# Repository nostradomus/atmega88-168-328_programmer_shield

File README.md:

# Atmega88/168/328 ISP programmer shield for Arduino UNO boards
  and    (minimal)

## What

This repo provides you with all necessary info (and files) to build an Arduino shield to program [Atmel](http://www.atmel.com)'s **[atmega88/168/328](http://www.microchip.com/design-centers/8-bit/microchip-avr-mcus)** 𝜇-controllers. For that matter, the underlying Arduino board should be loaded with the [ISP-programmer sketch](source/ArduinoISP.ino) (built-in example). Two versions have been included. All images in the description below, refer to the 16MHz version with an external crystal oscillator. An alternative (minimalistic) version is also available in all respective sub-folders (marked as 'minimal'). It concerns a shield to program the same µ-controllers using their 8MHz internal clock.

## Why

After having tested one of your new marvelous ideas with an existing eco-system, a lot of airwires and a piece of breadboard, you will probably start designing a state-of-the-art custom pcb to finalize the building of your project. During such a design phase, I however got tired of wiring up the ISPC connector over-and-over-again. As (like many people) I was having a spare UNO, which could serve as an [in-circuit serial programmer](https://en.wikipedia.org/wiki/In-system_programming), I decided to design a minimalistic shield to fit on top of it.  

## How

The shield has been designed with EAGLE from AutoDesk/CadSoft. This shield [project](eagle-files/) can be opened with the free version [(download here)](http://www.autodesk.com/products/eagle/free-download). Only [through-hole components](BOM.md) have been used in order to make the build also feasible for any junior electronics enthusiast. In the [pdf-folder](pdf-files/) of this repo pdf versions of all important EAGLE views are available, for those not wanting to install EAGLE. Pay attention to print the bottom and top-layer layouts **without re-sizing** (1:1). To have the printed circuit board built by a commercial PCB-shop, the full  [gerber-files](gerber-files/) are also available. When etching the board at home, don't forget to add the vias, or solder pieces of wire from solder to component side.

Currently, unpopulated boards for both the full and minimalistic version are still available from our workshop. If interested, [contact us via   :email:](http://nostradomus.ddns.net/contactform.html).

## Technical details

### What’s on the board

The board has been fit with a narrow 28-pin [ZIF](https://en.wikipedia.org/wiki/Zero_insertion_force) socket, which is wired up to be universal for several types of AVR's. On the boarder of the PCB, pin headers with double functionality have been mounted. Pins on the bottom-side to fit on the Arduino board, and feed-through female headers on the top for easy access of all Arduino connections.
The push button, is connected to the reset lines of the [AVR](https://en.wikipedia.org/wiki/Atmel_AVR) in the ZIF socket (and the ICSP on the shield) with a 10kΩ pull-up resistor. When the shield is cut correctly, the reset button for the underlying Arduino UNO should still be accessible. In order to make the Arduino Uno work as an ISP programmer a 10µF capacitor needs to be connected on its reset-line.
Three LED’s are available to visualize the correct functionality of the programming procedure.
An optional AVR ISP connector has been foreseen in order to use the shield as stand-alone with a commercial programmer.

#### BOM - bill of materials

Part   | Value          | Package      | Description  
------ | -------------- | ------------ | -----------                            
R1     | 10kΩ           | 0207/7       | resistor                                            
R2,3,4 | 470Ω           | 0204/5       | resistor                                            
C1     | 10µF/16V       | E2,5-6E      | polarized capacitor                                 
C2     | 100nF          | C050-025X075 | capacitor                                           
C3,4   | 22pF           | C2.5-2       | capacitor (version with xtal-oscillator)                                          
X1     | 16MHz          | QS           | oscillator crystal (version with xtal-oscillator)
LED1   | 3mm yellow     | 3mm          | LED                              
LED2   | 3mm red        | 3mm          | LED                              
LED3   | 3mm green      | 3mm          | LED
IC1    | 28-pin         | ZIF28-N      | 28-pin narrow ZIF-socket
ICSP1  | 2x3 pin-header | 2x3          | AVR ISP-6 Serial Programming Header (optional)
S1     | momentary      | 6x6x6mm      | momentary tact push button
S2     | toggle         | 9x4mm        | mini toggle switch
CON1   | 6-pin          | SIL06        | long needle female stackable pin header strip
CON2,3 | 8-pin          | SIL08        | long needle female stackable pin header strip
CON4   | 10-pin         | SIL10        | long needle female stackable pin header strip

### How things work

First the the [ISP-programmer sketch](sketches/ArduinoISP.ino) (built-in example) should be loaded to the Arduino UNO board. During that operation, switch S2 should be set to "RUN". Select “Arduino Uno” as target board in the tools-menu. Load the ISP-programmer sketch with the “UPLOAD” button. Once loaded, switch S2 can be set to "PROG" to send a sketch to the atmega 𝜇-controller in the ZIF socket.

To load a sketch to your atmega 𝜇-controller in the ZIF socket, make sure that the correct target board is selected in the tools-menu (you might need to download a specific library -> tools-menu, board manager). This time, use the “UPLOAD USING PROGRAMMER” option from the sketch-menu.

When using the "8MHz internal clock" shield, an [adapted board configuration](source/minimal-boards.zip) should be used (read "fuse-settings"), which can be found in the [source-folder](source/). Other versions can be found on the [Arduino website](https://www.arduino.cc/en/Tutorial/ArduinoToBreadboard) (see paragraph on minimal hardware). To install this package driver, create a "hardware" folder in the Arduino sketches folder on your computer (path to be found in the Arduino preferences),

and copy the unzipped [package archive](source/minimal-boards.zip) in there.

Next restart the Arduino IDE, and the required board will appear in your board's list.

When loading a new sketch to the target µ-controller, the 3 LED’s will tell you how things are going :
 - Green  : **ICSP programmer running** (fading LED means 'idle')
 - Yellow : **uploading sketch** (programming code is being uploaded)
 - Red    : **Error!** (oops, something went wrong during the upload)

### Proof of concept

So far, I have tested the shield with the below list of 𝜇-controllers :
- atmega168
- atmega328

 Programming shield should also function correctly for other pin-compatible µ-controllers, such as :
 - atmega88

## Contributors

If you are having any good suggestions, just drop me a line [:email:](http://nostradomus.ddns.net/contactform.html).
If feasible, I'll be happy to implement any proposed improvements.
And if you are having lots of time, I'll be happy to share the work with you ;-).

When you create your own version, don't forget to send us some nice pictures of your construction. We'll be happy to publish them in the :confetti_ball:Hall of Fame:confetti_ball:.

## :globe_with_meridians: License

At this moment, there is no specific license attached to this project.

So, today, if you like it, have fun with it (at your own risk of course :-D), and especially, be creative.

Oh, and when using anything from this repository, it is highly appreciated if you mention its origin.

If you would like to use any of this work (or the whole project) for commercial use, first [contact us :email:](http://nostradomus.ddns.net/contactform.html), so we can add the appropriate license, which best fits your business.

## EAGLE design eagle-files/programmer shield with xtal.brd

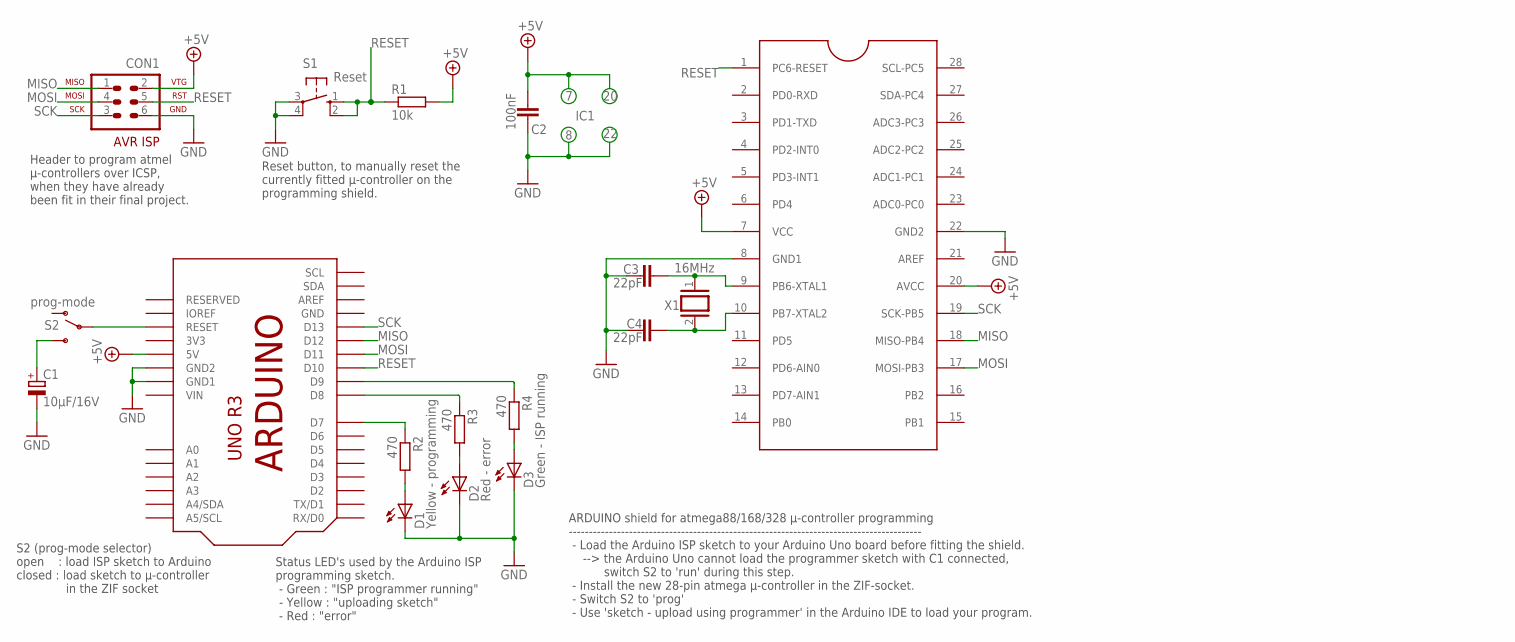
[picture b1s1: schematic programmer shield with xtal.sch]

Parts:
C1: 10µF/16V; E2,5-6E
C2: 100nF; C050-025X075
C3, C4: 22pF; C2.5-2
CON1: ICSP; AVR-ISP-6
D1: Yellow - programming; LED3MM
D2: Red - error; LED3MM
D3: Green - ISP running; LED3MM
IC1: Atmega88/168/328; DIL28-3-ZIF_NARROW
R1: 10k; 0207/7
R2, R3, R4: 470; 0204/5
S1: Reset; B3F-10XX
S2: prog-mode; MINI_SPDT_SWITCH-9.0X4.0MM
U$1: Arduino Uno; ARDUINO-R3
X1: 16MHz; QS

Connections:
3V3: U$1.3V (3V3)
+UB: C2.2, CON1.2, IC1.7 (VCC), IC1.20 (AVCC), R1.2, U$1.5V
GND: C1.-, C2.1, C3.1, C4.1, CON1.6, D1.K (C), D2.K (C), D3.K (C), IC1.8 (GND1), IC1.22 (GND2), S1.3, S1.4 (P1), U$1.GND, U$1.GND1, U$1.GND2
MISO: CON1.1, IC1.18 (MISO-PB4), U$1.D12
MOSI: CON1.4, IC1.17 (MOSI-PB3), U$1.D11
unnamed: C1.+, S2.3 (S)
unnamed: R4.1, U$1.D9
unnamed: R2.1, U$1.D7
unnamed: R3.1, U$1.D8
unnamed: D1.A, R2.2
unnamed: D2.A, R3.2
unnamed: D3.A, R4.2
unnamed: C3.2, IC1.9 (PB6-XTAL1), X1.1
unnamed: C4.2, IC1.10 (PB7-XTAL2), X1.2
unnamed: S2.2, U$1.RESET
RESET: CON1.5, IC1.1 (PC6-RESET), R1.1, S1.1 (S), S1.2 (S1), U$1.D10
SCK: CON1.3, IC1.19 (SCK-PB5), U$1.D13
VIN: U$1.VIN

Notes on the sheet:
IC1
Header to program atmel µ-controllers over ICSP, when they have already been fit in their final project.
Reset button, to manually reset the currently fitted µ-controller on the programming shield.
Status LED's used by the Arduino ISP programming sketch. - Green : "ISP programmer running" - Yellow : "uploading sketch" - Red : "error"
ARDUINO shield for atmega88/168/328 µ-controller programming ---------------------------------------------------------------------------------------- - Load the Arduino ISP sketch to your Arduino Uno board before fitting the shield. --> the Arduino Uno cannot load the programmer sketch with C1 conn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
S2 (prog-mode selector) open : load ISP sketch to Arduino closed : load sketch to µ-controller in the ZIF socket

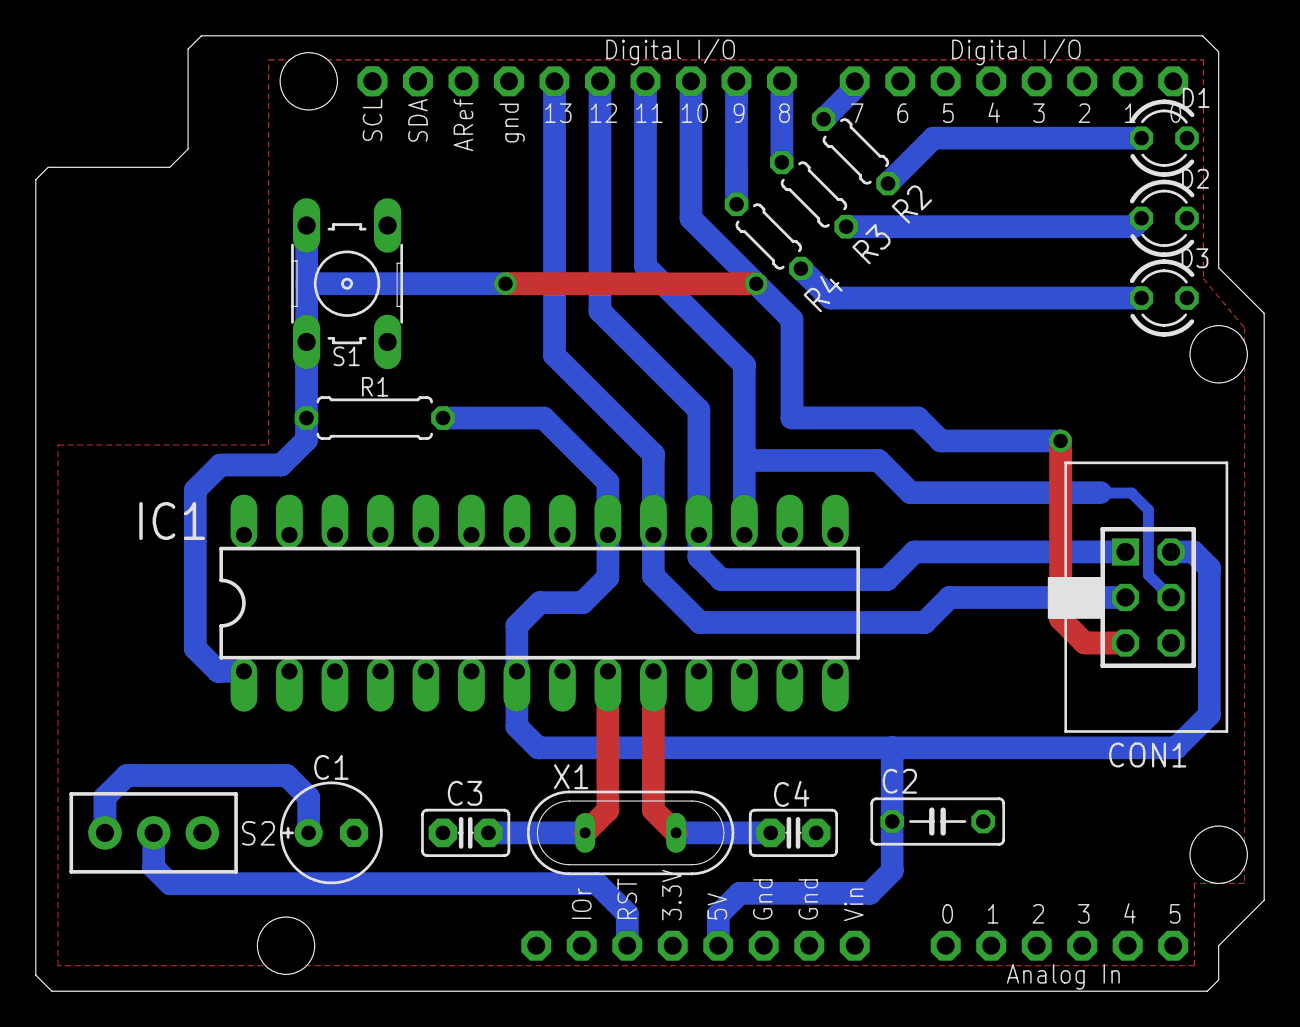
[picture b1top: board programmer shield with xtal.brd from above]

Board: 2 copper layers, 68.6 x 53.3 mm, 23 parts (1 on the bottom side), 16 nets.

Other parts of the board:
U$2: COPYRIGHT-LOGO-3-B
U$3, U$7: 3X-LOGO-10-B
U$4: COPYRIGHT-LOGO-3-T
U$5: 3X-LOGO-5-B
U$6: 3X-LOGO-5-T

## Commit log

2024-01-26 OS upgrade
